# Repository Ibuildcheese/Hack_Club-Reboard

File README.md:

# The ReBoard
This is an 87 key custom ANSI mechanical keyboard with a Raspberry Pi Pico microcontroller using QMK Software to program the Pico. All keys in the firmware are 100% ANSI and I am using Cherry MX Blue switches.

### Why/how i made this
Firstly, i want to say that this will be the first PCB that i have ever made and it was all because i thought making a new keyboard would be easier than cleaning my old one. My dell keyboard, sk-8125, my dad bought before i was born, and it was discontinued 10 years ago, so i comitted myself to making a keyboard better than something from that time period by myself. Firstly, I looked up a bunch of tutorial videos but since they didn't help me at all i decided to just get started and go from there however, there was a lot of time in between from waiting on a friend to answer a question i had to having to completely scrapping my initial 100% keyboard i had in mind because of some fatal errors i made during the schematic. With the amount of issues and redos i encountered, i never would have thought i'd finish in time, let alone ~15 days before the deadline. Even though all this inexperience did come at a cost (i.e. spending 3 whole days to find a 3d-model of a cherry MX switch) i still cant thank Hack Club enough for giving me the opportunity to actually get started making amazing projects like these and being able to learn and problem solve along the way.

### Completion Chart

| Name | Status | Extra |
| :-: | :-: | :-: |
| PCB | Designed and order ready |  |
| PCB-Parts | Chosen, order ready |  |
| Case | Designed, not yet printed |  |
| Firmware | Configured, not yet tested on hardware |  |

___

## Screenshots of Design: 
| PCB - Front - Rendered | PCB - Back Rendered |
| :-: | :-: |
|  |  |
| PCB - Editor - No-Silk | PCB - Editor - Silk |
|  |  |

| Schematic | 
| - |
|  |

| CAD - Render - Main |
| - |
|  |

| CAD - Render - Top | Cad - Render - Bottom |
| - | - |
|  |  |

___

## BOM

| Amt | Name | Price | Link | Extra |
| - | - | - | - | - |
| x90 | Cherry MX Blue Switches | $34.50 | [Link](https://www.aliexpress.us/item/3256806124797516.html?) | Color: Blue, 90pcs |
| x98 | Cherry Profile Keycaps | $11.72 | [Link](https://www.aliexpress.us/item/3256808041449227.html?) | color: beige |
| x5 | Stabilizers | $0.99 | [Link](https://www.aliexpress.us/item/2251832533420646.html?) | 1x6.25 (6u or 7u) + 4x2u |
| x100 | Diodes | $1.30 | [Link](https://www.aliexpress.us/item/3256807350544438.html?) | 100pc option |
| 1x | PCB | $21.35 | [Link](https://jlcpcb.com) | --- |
| 1x | 3d Printed Case | --- | --- | I will print it myself |
| 1x | Raspberry Pi Pico | $3.75 | [Link](https://www.aliexpress.us/item/3256806652932348.html?) | --- |
| --- | Total | $73.61 | --- | --- |

| BOM - Screenshot - PCB |
| :-: |
|  |
| BOM - Screenshot - AliExpress |
|  |

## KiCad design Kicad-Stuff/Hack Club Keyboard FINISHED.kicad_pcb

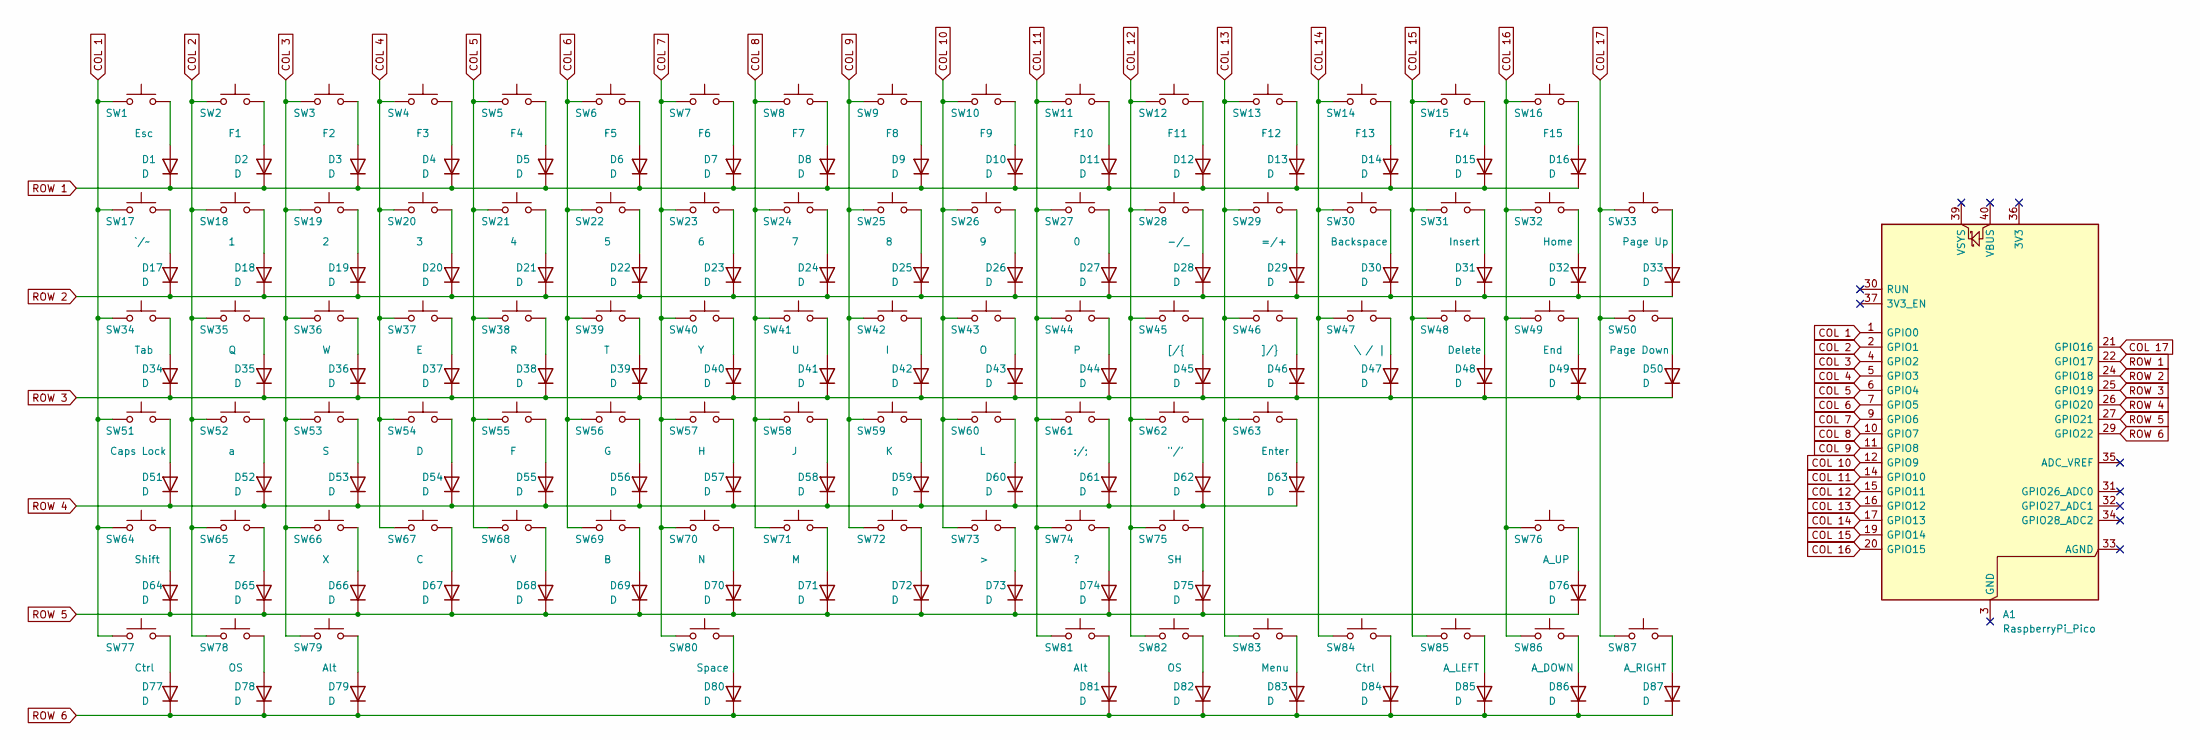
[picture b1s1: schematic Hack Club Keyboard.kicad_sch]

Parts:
A1: RaspberryPi_Pico; RaspberryPi_Pico_Common_Unspecified
D1, D2, D3, D4, D5, D6, D7, D8, D9, D10, D11, D12, D13, D14, D15, D16, D17, D18, D19, D20, D21, D22, D23, D24, D25, D26, D27, D28, D29, D30, D31, D32, D33, D34, D35, D36, D37, D38, D39, D40, D41, D42, D43, D44, D45, D46, D47, D48, D49, D50, D51, D52, D53, D54, D55, D56, D57, D58, D59, D60, D61, D62, D63, D64, D65, D66, D67, D68, D69, D70, D71, D72, D73, D74, D75, D76, D77, D78, D79, D80, D81, D82, D83, D84, D85, D86, D87: D; D_SOD-123
SW1: Esc; SW_Cherry_MX_1.00u_PCB
SW2: F1; SW_Cherry_MX_1.00u_PCB
SW3: F2; SW_Cherry_MX_1.00u_PCB
SW4: F3; SW_Cherry_MX_1.00u_PCB
SW5: F4; SW_Cherry_MX_1.00u_PCB
SW6: F5; SW_Cherry_MX_1.00u_PCB
SW7: F6; SW_Cherry_MX_1.00u_PCB
SW8: F7; SW_Cherry_MX_1.00u_PCB
SW9: F8; SW_Cherry_MX_1.00u_PCB
SW10: F9; SW_Cherry_MX_1.00u_PCB
SW11: F10; SW_Cherry_MX_1.00u_PCB
SW12: F11; SW_Cherry_MX_1.00u_PCB
SW13: F12; SW_Cherry_MX_1.00u_PCB
SW14: F13; SW_Cherry_MX_1.00u_PCB
SW15: F14; SW_Cherry_MX_1.00u_PCB
SW16: F15; SW_Cherry_MX_1.00u_PCB
SW17: `/~; SW_Cherry_MX_1.00u_PCB
SW18: 1; SW_Cherry_MX_1.00u_PCB
SW19: 2; SW_Cherry_MX_1.00u_PCB
SW20: 3; SW_Cherry_MX_1.00u_PCB
SW21: 4; SW_Cherry_MX_1.00u_PCB
SW22: 5; SW_Cherry_MX_1.00u_PCB
SW23: 6; SW_Cherry_MX_1.00u_PCB
SW24: 7; SW_Cherry_MX_1.00u_PCB
SW25: 8; SW_Cherry_MX_1.00u_PCB
SW26: 9; SW_Cherry_MX_1.00u_PCB
SW27: 0; SW_Cherry_MX_1.00u_PCB
SW28: -/_; SW_Cherry_MX_1.00u_PCB
SW29: =/+; SW_Cherry_MX_1.00u_PCB
SW30: Backspace; SW_Cherry_MX_2.00u_PCB
SW31: Insert; SW_Cherry_MX_1.00u_PCB
SW32: Home; SW_Cherry_MX_1.00u_PCB
SW33: Page Up; SW_Cherry_MX_1.00u_PCB
SW34: Tab; SW_Cherry_MX_1.50u_PCB
SW35: Q; SW_Cherry_MX_1.00u_PCB
SW36: W; SW_Cherry_MX_1.00u_PCB
SW37: E; SW_Cherry_MX_1.00u_PCB
SW38: R; SW_Cherry_MX_1.00u_PCB
SW39: T; SW_Cherry_MX_1.00u_PCB
SW40: Y; SW_Cherry_MX_1.00u_PCB
SW41: U; SW_Cherry_MX_1.00u_PCB
SW42: I; SW_Cherry_MX_1.00u_PCB
SW43: O; SW_Cherry_MX_1.00u_PCB
SW44: P; SW_Cherry_MX_1.00u_PCB
SW45: [/{; SW_Cherry_MX_1.00u_PCB
SW46: ]/}; SW_Cherry_MX_1.00u_PCB
SW47: \ / |; SW_Cherry_MX_1.50u_PCB
SW48: Delete; SW_Cherry_MX_1.00u_PCB
SW49: End; SW_Cherry_MX_1.00u_PCB
SW50: Page Down; SW_Cherry_MX_1.00u_PCB
SW51: Caps Lock; SW_Cherry_MX_1.75u_PCB
SW52: a; SW_Cherry_MX_1.00u_PCB
SW53: S; SW_Cherry_MX_1.00u_PCB
SW54: D; SW_Cherry_MX_1.00u_PCB
SW55: F; SW_Cherry_MX_1.00u_PCB
SW56: G; SW_Cherry_MX_1.00u_PCB
SW57: H; SW_Cherry_MX_1.00u_PCB
SW58: J; SW_Cherry_MX_1.00u_PCB
SW59: K; SW_Cherry_MX_1.00u_PCB
SW60: L; SW_Cherry_MX_1.00u_PCB
SW61: :/;; SW_Cherry_MX_1.00u_PCB
SW62: "/'; SW_Cherry_MX_1.00u_PCB
SW63: Enter; SW_Cherry_MX_2.25u_PCB
SW64: Shift; SW_Cherry_MX_2.25u_PCB
SW65: Z; SW_Cherry_MX_1.00u_PCB
SW66: X; SW_Cherry_MX_1.00u_PCB
SW67: C; SW_Cherry_MX_1.00u_PCB
SW68: V; SW_Cherry_MX_1.00u_PCB
SW69: B; SW_Cherry_MX_1.00u_PCB
SW70: N; SW_Cherry_MX_1.00u_PCB
SW71: M; SW_Cherry_MX_1.00u_PCB
SW72: SW_Cherry_MX_1.00u_PCB
SW73: >; SW_Cherry_MX_1.00u_PCB
SW74: ?; SW_Cherry_MX_1.00u_PCB
SW75: SH; SW_Cherry_MX_2.75u_PCB
SW76: A_UP; SW_Cherry_MX_1.00u_PCB
SW77, SW84: Ctrl; SW_Cherry_MX_1.25u_PCB
SW78, SW82: OS; SW_Cherry_MX_1.25u_PCB
SW79, SW81: Alt; SW_Cherry_MX_1.25u_PCB
SW80: Space; SW_Cherry_MX_6.25u_PCB
SW83: Menu; SW_Cherry_MX_1.25u_PCB
SW85: A_LEFT; SW_Cherry_MX_1.00u_PCB
SW86: A_DOWN; SW_Cherry_MX_1.00u_PCB
SW87: A_RIGHT; SW_Cherry_MX_1.00u_PCB

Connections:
COL 1: A1.1 (GPIO0), SW1.1, SW17.1, SW34.1, SW51.1, SW64.1, SW77.1
COL 2: A1.2 (GPIO1), SW2.1, SW18.1, SW35.1, SW52.1, SW65.1, SW78.1
COL 3: A1.4 (GPIO2), SW3.1, SW19.1, SW36.1, SW53.1, SW66.1, SW79.1
COL 4: A1.5 (GPIO3), SW4.1, SW20.1, SW37.1, SW54.1, SW67.1
COL 5: A1.6 (GPIO4), SW5.1, SW21.1, SW38.1, SW55.1, SW68.1
COL 6: A1.7 (GPIO5), SW6.1, SW22.1, SW39.1, SW56.1, SW69.1
COL 7: A1.9 (GPIO6), SW7.1, SW23.1, SW40.1, SW57.1, SW70.1, SW80.1
COL 8: A1.10 (GPIO7), SW8.1, SW24.1, SW41.1, SW58.1, SW71.1
COL 9: A1.11 (GPIO8), SW9.1, SW25.1, SW42.1, SW59.1, SW72.1
COL 10: A1.12 (GPIO9), SW10.1, SW26.1, SW43.1, SW60.1, SW73.1
COL 11: A1.14 (GPIO10), SW11.1, SW27.1, SW44.1, SW61.1, SW74.1, SW81.1
COL 12: A1.15 (GPIO11), SW12.1, SW28.1, SW45.1, SW62.1, SW75.1, SW82.1
COL 13: A1.16 (GPIO12), SW13.1, SW29.1, SW46.1, SW63.1, SW83.1
COL 14: A1.17 (GPIO13), SW14.1, SW30.1, SW47.1, SW84.1
COL 15: A1.19 (GPIO14), SW15.1, SW31.1, SW48.1, SW85.1
COL 16: A1.20 (GPIO15), SW16.1, SW32.1, SW49.1, SW76.1, SW86.1
COL 17: A1.21 (GPIO16), SW33.1, SW50.1, SW87.1
unnamed: D1.2 (A), SW1.2
unnamed: D2.2 (A), SW2.2
unnamed: D3.2 (A), SW3.2
unnamed: D4.2 (A), SW4.2
unnamed: D5.2 (A), SW5.2
unnamed: D6.2 (A), SW6.2
unnamed: D7.2 (A), SW7.2
unnamed: D8.2 (A), SW8.2
unnamed: D9.2 (A), SW9.2
unnamed: D10.2 (A), SW10.2
unnamed: D11.2 (A), SW11.2
unnamed: D12.2 (A), SW12.2
unnamed: D13.2 (A), SW13.2
unnamed: D14.2 (A), SW14.2
unnamed: D15.2 (A), SW15.2
unnamed: D16.2 (A), SW16.2
unnamed: D17.2 (A), SW17.2
unnamed: D18.2 (A), SW18.2
unnamed: D19.2 (A), SW19.2
unnamed: D20.2 (A), SW20.2
unnamed: D21.2 (A), SW21.2
unnamed: D22.2 (A), SW22.2
unnamed: D23.2 (A), SW23.2
unnamed: D24.2 (A), SW24.2
unnamed: D25.2 (A), SW25.2
unnamed: D26.2 (A), SW26.2
unnamed: D27.2 (A), SW27.2
unnamed: D28.2 (A), SW28.2
unnamed: D29.2 (A), SW29.2
unnamed: D30.2 (A), SW30.2
unnamed: D31.2 (A), SW31.2
unnamed: D32.2 (A), SW32.2
unnamed: D33.2 (A), SW33.2
unnamed: D34.2 (A), SW34.2
unnamed: D35.2 (A), SW35.2
unnamed: D36.2 (A), SW36.2
unnamed: D37.2 (A), SW37.2
unnamed: D38.2 (A), SW38.2
unnamed: D39.2 (A), SW39.2
unnamed: D40.2 (A), SW40.2
unnamed: D41.2 (A), SW41.2
unnamed: D42.2 (A), SW42.2
unnamed: D43.2 (A), SW43.2
unnamed: D44.2 (A), SW44.2
unnamed: D45.2 (A), SW45.2
unnamed: D46.2 (A), SW46.2
unnamed: D47.2 (A), SW47.2
unnamed: D48.2 (A), SW48.2
unnamed: D49.2 (A), SW49.2
unnamed: D50.2 (A), SW50.2
unnamed: D51.2 (A), SW51.2
unnamed: D52.2 (A), SW52.2
unnamed: D53.2 (A), SW53.2
unnamed: D54.2 (A), SW54.2
unnamed: D55.2 (A), SW55.2
unnamed: D56.2 (A), SW56.2
unnamed: D57.2 (A), SW57.2
unnamed: D58.2 (A), SW58.2
unnamed: D59.2 (A), SW59.2
unnamed: D60.2 (A), SW60.2
unnamed: D61.2 (A), SW61.2
unnamed: D62.2 (A), SW62.2
unnamed: D63.2 (A), SW63.2
unnamed: D64.2 (A), SW64.2
unnamed: D65.2 (A), SW65.2
unnamed: D66.2 (A), SW66.2
unnamed: D67.2 (A), SW67.2
unnamed: D68.2 (A), SW68.2
unnamed: D69.2 (A), SW69.2
unnamed: D70.2 (A), SW70.2
unnamed: D71.2 (A), SW71.2
unnamed: D72.2 (A), SW72.2
unnamed: D73.2 (A), SW73.2
unnamed: D74.2 (A), SW74.2
unnamed: D75.2 (A), SW75.2
unnamed: D76.2 (A), SW76.2
unnamed: D77.2 (A), SW77.2
unnamed: D78.2 (A), SW78.2
unnamed: D79.2 (A), SW79.2
unnamed: D80.2 (A), SW80.2
unnamed: D81.2 (A), SW81.2
unnamed: D82.2 (A), SW82.2
unnamed: D83.2 (A), SW83.2
unnamed: D84.2 (A), SW84.2
unnamed: D85.2 (A), SW85.2
unnamed: D86.2 (A), SW86.2
unnamed: D87.2 (A), SW87.2
ROW 1: A1.22 (GPIO17), D1.1 (K), D2.1 (K), D3.1 (K), D4.1 (K), D5.1 (K), D6.1 (K), D7.1 (K), D8.1 (K), D9.1 (K), D10.1 (K), D11.1 (K), D12.1 (K), D13.1 (K), D14.1 (K), D15.1 (K), D16.1 (K)
ROW 2: A1.24 (GPIO18), D17.1 (K), D18.1 (K), D19.1 (K), D20.1 (K), D21.1 (K), D22.1 (K), D23.1 (K), D24.1 (K), D25.1 (K), D26.1 (K), D27.1 (K), D28.1 (K), D29.1 (K), D30.1 (K), D31.1 (K), D32.1 (K), D33.1 (K)
ROW 3: A1.25 (GPIO19), D34.1 (K), D35.1 (K), D36.1 (K), D37.1 (K), D38.1 (K), D39.1 (K), D40.1 (K), D41.1 (K), D42.1 (K), D43.1 (K), D44.1 (K), D45.1 (K), D46.1 (K), D47.1 (K), D48.1 (K), D49.1 (K), D50.1 (K)
ROW 4: A1.26 (GPIO20), D51.1 (K), D52.1 (K), D53.1 (K), D54.1 (K), D55.1 (K), D56.1 (K), D57.1 (K), D58.1 (K), D59.1 (K), D60.1 (K), D61.1 (K), D62.1 (K), D63.1 (K)
ROW 5: A1.27 (GPIO21), D64.1 (K), D65.1 (K), D66.1 (K), D67.1 (K), D68.1 (K), D69.1 (K), D70.1 (K), D71.1 (K), D72.1 (K), D73.1 (K), D74.1 (K), D75.1 (K), D76.1 (K)
ROW 6: A1.29 (GPIO22), D77.1 (K), D78.1 (K), D79.1 (K), D80.1 (K), D81.1 (K), D82.1 (K), D83.1 (K), D84.1 (K), D85.1 (K), D86.1 (K), D87.1 (K)

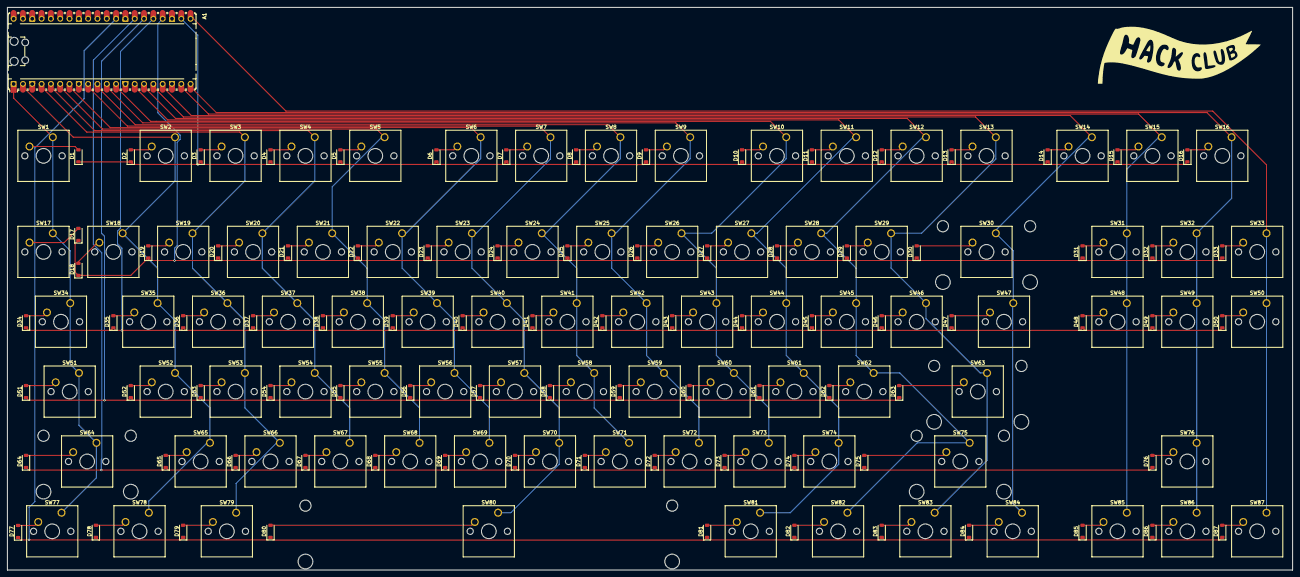
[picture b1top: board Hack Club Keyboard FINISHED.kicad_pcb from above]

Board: 2 copper layers, 350.5 x 153.4 mm, 175 parts (0 on the bottom side), 110 nets.

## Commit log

2026-01-05 Create Kicad Stuff
2026-01-05 add Kicad Files
2026-01-10 Create f
2026-01-10 Create Screenshots_PCB_3D
2026-01-10 Create f2
2026-01-14 Update README.md -- TOTAL
2026-01-14 Update README.md - BOM
